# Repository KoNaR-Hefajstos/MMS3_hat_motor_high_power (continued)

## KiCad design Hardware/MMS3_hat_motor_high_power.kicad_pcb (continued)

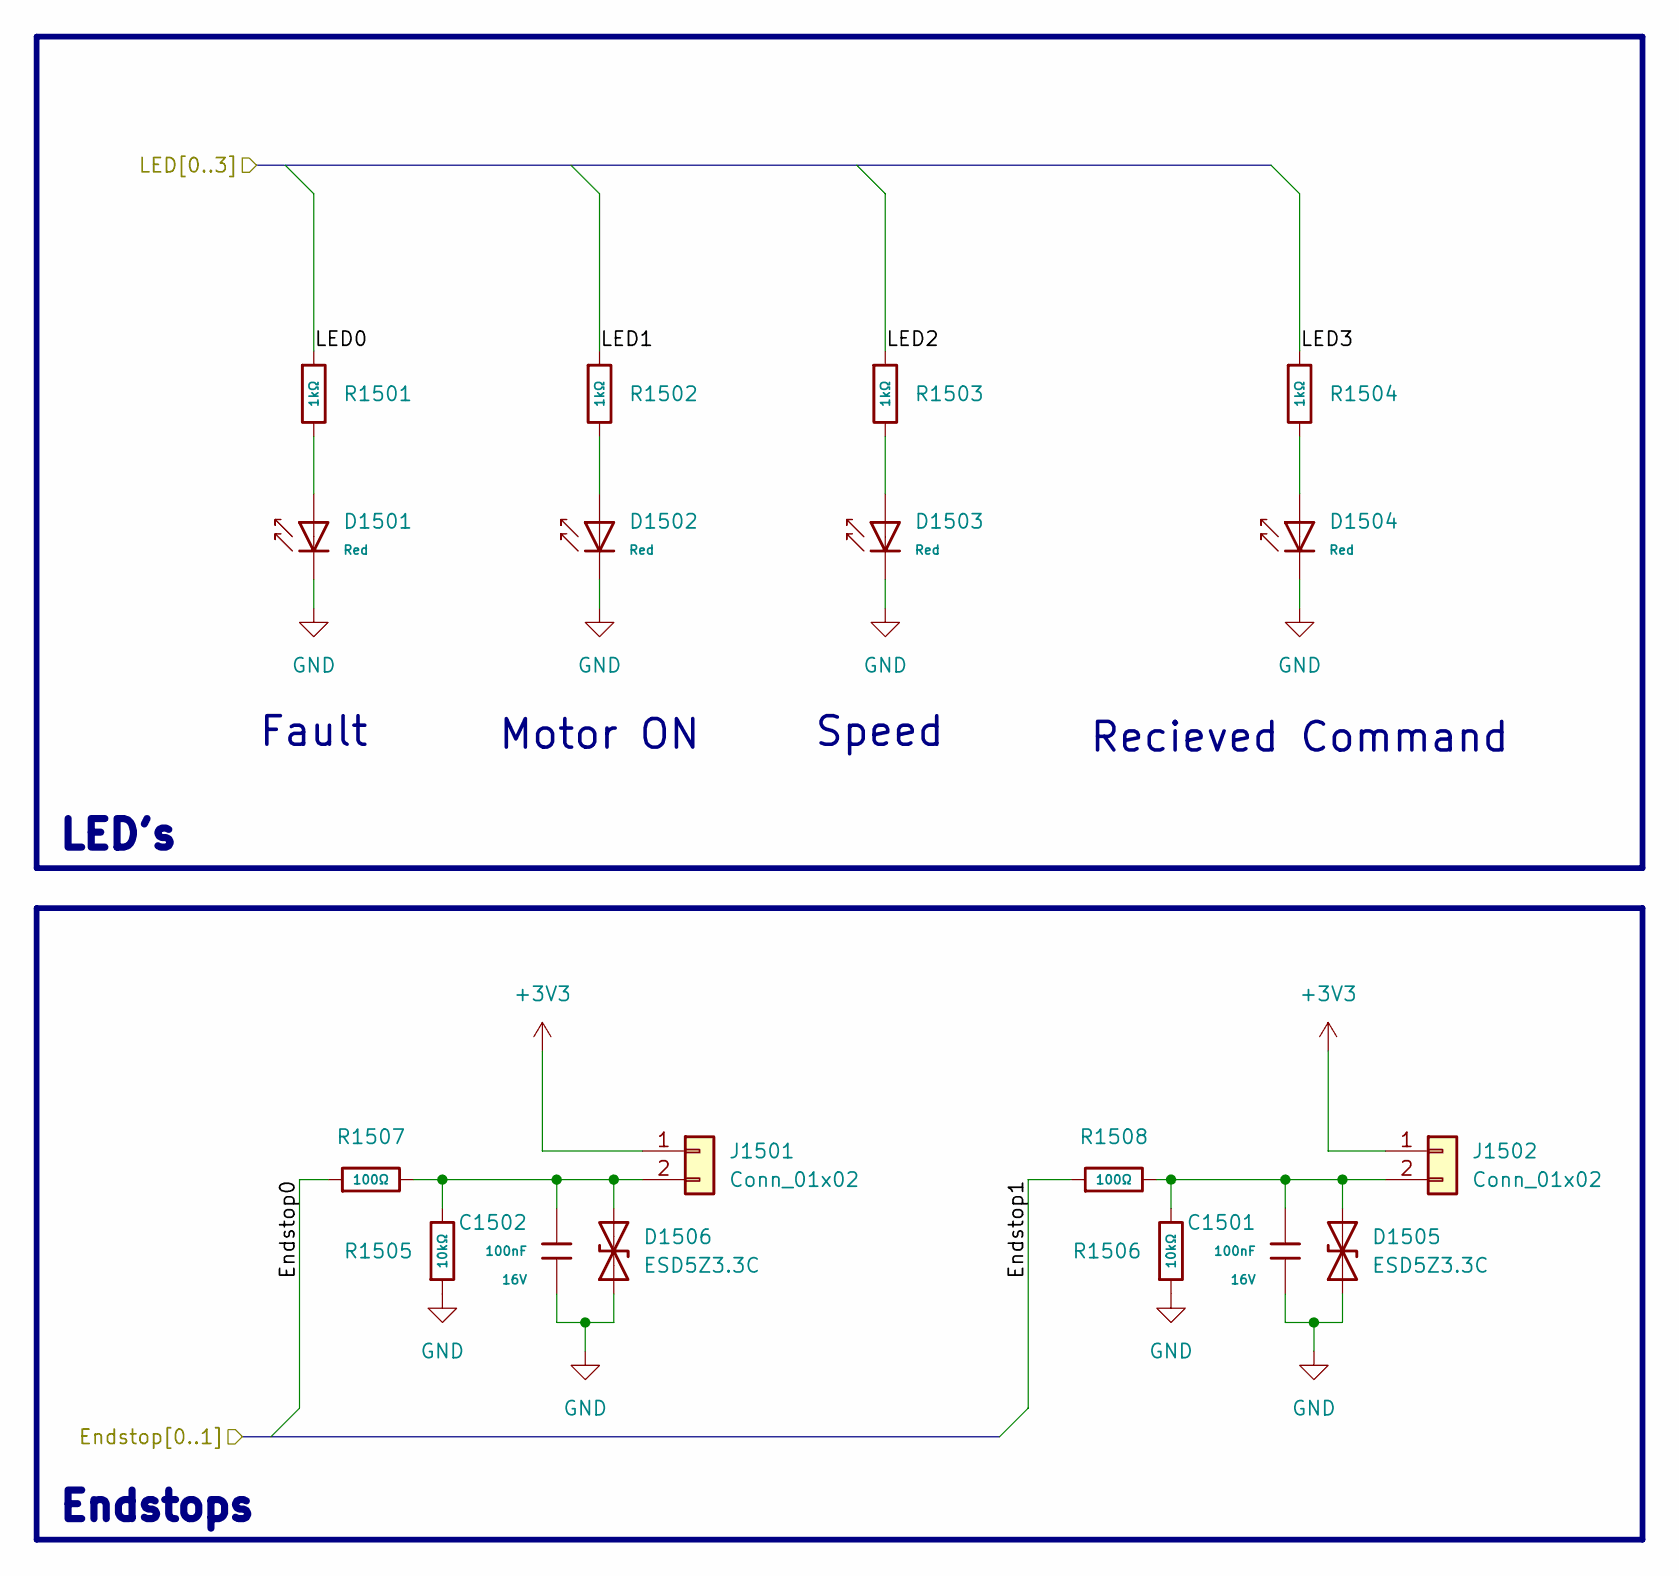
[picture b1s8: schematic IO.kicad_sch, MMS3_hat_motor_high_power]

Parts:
C1501, C1502: 100nF; C_0402; Voltage Rated 16V; Tolerance ±10%; Part CL05B104KO5NNNC; LCSC C1525
D1501, D1502, D1503, D1504: Red; D_0603; Part KT-0603R; LCSC C2286
D1505, D1506: ESD5Z3.3C; D_SOD-523; LCSC C502551
J1501, J1502: Conn_01x02; JST_XH_S2B-XH-A-1_1x02_P2.50mm_Horizontal
R1501, R1502, R1503, R1504: 1kΩ; R_0402; Overload Voltage (Max) 50V; Tolerance ±1%; Part 0402WGF1001TCE; LCSC C11702
R1505, R1506: 10kΩ; R_0402; Overload Voltage (Max) 50V; Tolerance ±1%; Part 0402WGF1002TCE; LCSC C25744
R1507, R1508: 100Ω; R_0402; Overload Voltage (Max) 50V; Tolerance ±1%; Part 0402WGF1000TCE; LCSC C25076

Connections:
+3V3: J1501.1, J1502.1; also elsewhere on the board
/User Area/CH32V305RBT6/GPIOB6: R1507.1; also elsewhere on the board
/User Area/CH32V305RBT6/GPIOB7: R1508.1; also elsewhere on the board
/User Area/CH32V305RBT6/GPIOB8: R1501.1; also elsewhere on the board
/User Area/CH32V305RBT6/GPIOB9: R1502.1; also elsewhere on the board
/User Area/CH32V305RBT6/GPIOB10: R1503.1; also elsewhere on the board
/User Area/CH32V305RBT6/GPIOB11: R1504.1; also elsewhere on the board
GND: C1501.2, C1502.2, D1501.1, D1502.1, D1503.1, D1504.1, D1505.1 (A1), D1506.1 (A1), R1505.1, R1506.1; also elsewhere on the board
unnamed: D1501.2, R1501.2
unnamed: D1502.2, R1502.2
unnamed: D1503.2, R1503.2
unnamed: D1504.2, R1504.2
unnamed: C1501.1, D1505.2 (A2), J1502.2, R1506.2, R1508.2
unnamed: C1502.1, D1506.2 (A2), J1501.2, R1505.2, R1507.2

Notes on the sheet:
LED's
Fault
Speed
Recieved Command
Motor ON
Endstops

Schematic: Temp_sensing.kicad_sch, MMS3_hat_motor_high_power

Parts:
R1401: 10kΩ; R_0402; Overload Voltage (Max) 50V; Tolerance ±1%; Part 0402WGF1002TCE; LCSC C25744
TH1401: NTC 10kΩ; R_0402; LCSC C77131

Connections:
+3V3: TH1401.1; also elsewhere on the board
/User Area/CH32V305RBT6/GPIOA3: R1401.1, TH1401.2; also elsewhere on the board
GND: R1401.2; also elsewhere on the board

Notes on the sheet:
BEHOLD! THE TEMPERATURE SENSING MACHINATIONS!

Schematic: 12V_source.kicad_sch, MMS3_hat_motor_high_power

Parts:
C1601: 33nF; C_0603; Voltage Rated 50V; Tolerance ±10%; Part CL10B333KB8NNNC; LCSC C21117
C1602: 33uF; CP_Radial_D10.0mm_P5.00mm; LCSC C56131621
C1603: 100uF; CP_Radial_D6.3mm_P2.50mm; LCSC C48935344
D1601: SS210; D_SMA; Forward Voltage (Vf@If) 850mV@2A; Reverse Voltage (Vr) 100V; Part SS210; LCSC C14996
L1601: SMDRI127-681MT; L_SXN_SMDRI127; MPN SMDRI127-681MT; LCSC Part C72434
R1601: 30kΩ; R_0603; Overload Voltage (Max) 75V; Tolerance ±1%; Part 0603WAF3002T5E; LCSC C22984
R1602: 3,48kΩ; R_0603; LCSC C2998120
U1602: XL7005A; SOIC-8-1EP_3.9x4.9mm_P1.27mm_EP2.41x3.3mm; MPN XL7005A; LCSC Part C50848

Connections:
+12V: C1601.1, C1603.1, L1601.2, R1601.1; also elsewhere on the board
/User Area/VIN: C1602.1, U1602.1 (VIN); also elsewhere on the board
GND: C1602.2, C1603.2, D1601.2, R1602.2, U1602.4 (EN), U1602.5 (GND), U1602.6 (GND), U1602.7 (GND), U1602.8 (GND), U1602.9; also elsewhere on the board
unnamed: C1601.2, R1601.2, R1602.1, U1602.3 (FB)
unnamed: D1601.1, L1601.1, U1602.2 (SW)

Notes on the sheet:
100% duty capable -> 12V = short

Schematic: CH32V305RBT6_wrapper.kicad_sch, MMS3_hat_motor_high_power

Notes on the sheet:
SPI/TIM for Encoder
CHECK IF TIM CHANNELS FOR MOTOR ARE GOOD (IF EACH ONE IS TIMxCHx + TIMxCHxN
ChainBus SPI
Mosfets & EN
USE TIM10 or SPI3
0-5 for BLDC 0-7 for Stepper
LEFT User usable GPIO
ADC's
LED's & Endstops
USE SPI1
MCU
USE TIM1 and TIM3

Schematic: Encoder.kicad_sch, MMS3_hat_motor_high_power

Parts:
D1301: 1SMA4729A; D_DO-214AC(SMA); Part 1SMA4729A; LCSC C19077475
D1302, D1303, D1304, D1305: ESD5Z3.3C; D_SOD-523; LCSC C502551
J1301: Conn_01x06; JST_XH_S6B-XH-A_1x06_P2.50mm_Horizontal
R1301, R1302, R1303, R1304: 100Ω; R_0402; Overload Voltage (Max) 50V; Tolerance ±1%; Part 0402WGF1000TCE; LCSC C25076

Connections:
+3V3: D1301.1, J1301.2; also elsewhere on the board
/User Area/CH32V305RBT6/GPIOA15: R1301.1; also elsewhere on the board
/User Area/CH32V305RBT6/GPIOB3: R1304.1; also elsewhere on the board
/User Area/CH32V305RBT6/GPIOB4: R1302.1; also elsewhere on the board
/User Area/CH32V305RBT6/GPIOB5: R1303.1; also elsewhere on the board
GND: D1301.2, D1302.1 (A1), D1303.1 (A1), D1304.1 (A1), D1305.1 (A1), J1301.1; also elsewhere on the board
unnamed: D1302.2 (A2), J1301.6, R1301.2
unnamed: D1303.2 (A2), J1301.5, R1302.2
unnamed: D1304.2 (A2), J1301.4, R1303.2
unnamed: D1305.2 (A2), J1301.3, R1304.2

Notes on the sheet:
Encoder Connector

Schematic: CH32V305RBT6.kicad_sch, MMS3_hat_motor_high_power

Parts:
C1101: 10uF; C_0603; Voltage Rated 10V; Tolerance ±10%; Part CL10A106KP8NNNC; LCSC C19702
C1102, C1109: 100nF; C_0402; Voltage Rated 50V; Tolerance ±10%; Part CL05B104KB54PNC; LCSC C307331
C1103, C1111: 22pF; C_0402; Voltage Rated 50V; Tolerance ±5%; Part 0402CG220J500NT; LCSC C1555
C1104, C1108: 12pF; C_0402; Voltage Rated 50V; Tolerance ±5%; Part 0402CG120J500NT; LCSC C1547
C1105, C1107, C1110, C1113, C1114: 100nF; C_0402; Voltage Rated 16V; Tolerance ±10%; Part CL05B104KO5NNNC; LCSC C1525
C1106, C1112: 10uF; C_0402; Voltage Rated 6.3V; Tolerance ±20%; Part CL05A106MQ5NUNC; LCSC C15525
D1101: Yellow; D_0603; Forward Voltage (VF) 1.6V~2.6V; Part NCD0603Y2; LCSC C89811
FB1101: FB_0603; Current Rating 200mA; Tolerance ±25%; Part GZ1608D601TF; LCSC C1002
J1101: WCH Link; PinSocket_2x05_P2.54mm_Vertical
R1101: 0Ω; R_0402; Overload Voltage (Max) 50V; Tolerance ±1%; Part 0402WGF0000TCE; LCSC C17168
R1102, R1103, R1104, R1106: 10kΩ; R_0402; Overload Voltage (Max) 50V; Tolerance ±1%; Part 0402WGF1002TCE; LCSC C25744
R1105: 10kΩ; R_0402; Overload Voltage (Max) 50V; Tolerance ±1%; Part 0402WGF1002TCE; LCSC C25744; not fitted
R1107: 1kΩ; R_0402; Overload Voltage (Max) 50V; Tolerance ±1%; Part 0402WGF1001TCE; LCSC C11702
S1101, S1102, S1103: Tactile Button, 160gf; SW_TS-1088-AR02016; Voltage Rating (Dc) 12V; Part TS-1088-AR02016; LCSC C720477
TP1101, TP1102: TestPoint; TestPoint_Pad_D1.0mm
U1101: CH32V305RBT6; C5187529_LQFP-64_L10_0-W10_0-P0_50-LS12_0-BL; LCSC C5187529
X1101: X322525MOB4SI; OSC-SMD_4P-L3.2-W2.5-BL; Frequency Tolerance ±10ppm; Part X322525MOB4SI; LCSC C9006
X1102: Q13FC1350000400; FC-135R_L3.2-W1.5; Frequency Tolerance ±20ppm; Part Q13FC13500004; LCSC C32346

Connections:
+3V3: C1101.1, C1102.1, C1105.1, C1106.1, C1107.1, C1110.1, FB1101.1, J1101.8, R1101.1, R1104.1, R1105.1, S1101.1 (A), S1102.1 (A), TP1101.1 (1_1), U1101.19 (VDD_4), U1101.32 (VIO_1), U1101.48 (VDD_2), U1101.64 (VIO_3); also elsewhere on the board
+5V: J1101.10; also elsewhere on the board
/User Area/ADC0: U1101.8 (PC0/ADC10); also elsewhere on the board
/User Area/ADC1: U1101.9 (PC1/ADC11); also elsewhere on the board
/User Area/ADC2: U1101.10 (PC2/ADC12); also elsewhere on the board
/User Area/ADC3: U1101.11 (PC3/ADC13); also elsewhere on the board
/User Area/ADC4: U1101.24 (PC4/ADC14); also elsewhere on the board
/User Area/ADC5: U1101.25 (PC5/ADC15); also elsewhere on the board
/User Area/ADC6: U1101.15 (PA1/ADC1); also elsewhere on the board
/User Area/ADC7: U1101.16 (PA2/ADC2); also elsewhere on the board
/User Area/CH32V305RBT6/CH32V305RBT6 minimal circuit/BOOT0: R1103.1, S1102.2 (B), U1101.60 (BOOT0)
/User Area/CH32V305RBT6/CH32V305RBT6 minimal circuit/NRST: C1114.1, J1101.9, R1104.2, S1103.1 (A), U1101.7 (NRST)
/User Area/CH32V305RBT6/CH32V305RBT6 minimal circuit/OSC32IN: C1104.1, U1101.3 (PC14/OSC32IN), X1102.1
/User Area/CH32V305RBT6/CH32V305RBT6 minimal circuit/OSC32OUT: C1108.1, U1101.4 (PC15/OSC32OUT), X1102.2
/User Area/CH32V305RBT6/CH32V305RBT6 minimal circuit/OSCIN: C1103.1, U1101.5 (OSC_IN/PD0), X1101.1 (OSC)
/User Area/CH32V305RBT6/CH32V305RBT6 minimal circuit/OSCOUT: C1111.1, U1101.6 (OSC_OUT/PD1), X1101.3 (OSC)
/User Area/CH32V305RBT6/CH32V305RBT6 minimal circuit/PB2/BOOT1: R1105.2, R1106.1, U1101.28 (PB2/BOOT1)
/User Area/CH32V305RBT6/CH32V305RBT6 minimal circuit/PC13/TAMPER-RTC: R1102.1, S1101.2 (B), U1101.2 (PC13/TAMPER-RTC)
/User Area/CH32V305RBT6/CH32V305RBT6 minimal circuit/PD2: R1107.1, U1101.54 (PD2)
/User Area/CH32V305RBT6/CH32V305RBT6 minimal circuit/SWCLK: J1101.2, U1101.49 (PA14/SWCLK)
/User Area/CH32V305RBT6/CH32V305RBT6 minimal circuit/SWDIO: J1101.4, U1101.46 (PA13/SWDIO)
/User Area/CH32V305RBT6/CH32V305RBT6 minimal circuit/UART4_RX: J1101.3, U1101.52 (PC11)
/User Area/CH32V305RBT6/CH32V305RBT6 minimal circuit/UART4_TX: J1101.1, U1101.51 (PC10)
/User Area/CH32V305RBT6/CH32V305RBT6 minimal circuit/VDDA: C1109.1, C1112.1, FB1101.2, TP1102.1 (1_1), U1101.13 (VDDA)
/User Area/CH32V305RBT6/GPIOA0: U1101.14 (PA0/WKUP/ADC0); also elsewhere on the board
/User Area/CH32V305RBT6/GPIOA3: U1101.17 (PA3/ADC3); also elsewhere on the board
/User Area/CH32V305RBT6/GPIOA11: U1101.44 (PA11/USB1DM)
/User Area/CH32V305RBT6/GPIOA12: U1101.45 (PA12/USB1DP)
/User Area/CH32V305RBT6/GPIOA15: U1101.50 (PA15); also elsewhere on the board
/User Area/CH32V305RBT6/GPIOB3: U1101.55 (PB3); also elsewhere on the board
/User Area/CH32V305RBT6/GPIOB4: U1101.56 (PB4); also elsewhere on the board
/User Area/CH32V305RBT6/GPIOB5: U1101.57 (PB5); also elsewhere on the board
/User Area/CH32V305RBT6/GPIOB6: U1101.58 (PB6/USB2DM); also elsewhere on the board
/User Area/CH32V305RBT6/GPIOB7: U1101.59 (PB7/USB2DP); also elsewhere on the board
/User Area/CH32V305RBT6/GPIOB8: U1101.61 (PB8); also elsewhere on the board
/User Area/CH32V305RBT6/GPIOB9: U1101.62 (PB9); also elsewhere on the board
/User Area/CH32V305RBT6/GPIOB10: U1101.29 (PB10); also elsewhere on the board
/User Area/CH32V305RBT6/GPIOB11: U1101.30 (PB11); also elsewhere on the board
/User Area/CH32V305RBT6/GPIOB12: U1101.33 (PB12); also elsewhere on the board
/User Area/CH32V305RBT6/GPIOC6: U1101.37 (PC6)
/User Area/CH32V305RBT6/GPIOC7: U1101.38 (PC7)
/User Area/CH32V305RBT6/GPIOC8: U1101.39 (PC8)
/User Area/CH32V305RBT6/GPIOC9: U1101.40 (PC9)
/User Area/CH32V305RBT6/GPIOC12: U1101.53 (PC12)
/User Area/Chainbus.CS: U1101.20 (PA4/ADC4/DAC0); also elsewhere on the board
/User Area/Chainbus.MISO: U1101.22 (PA6/ADC6); also elsewhere on the board
/User Area/Chainbus.MOSI: U1101.23 (PA7/ADC7); also elsewhere on the board
/User Area/Chainbus.SCK: U1101.21 (PA5/ADC5/DAC1); also elsewhere on the board
/User Area/Mosfet0: U1101.41 (PA8); also elsewhere on the board
/User Area/Mosfet1: U1101.34 (PB13); also elsewhere on the board
/User Area/Mosfet2: U1101.42 (PA9); also elsewhere on the board
/User Area/Mosfet3: U1101.35 (PB14); also elsewhere on the board
/User Area/Mosfet4: U1101.43 (PA10); also elsewhere on the board
/User Area/Mosfet5: U1101.36 (PB15); also elsewhere on the board
/User Area/Mosfet6: U1101.26 (PB0/ADC8); also elsewhere on the board
/User Area/Mosfet7: U1101.27 (PB1/ADC9); also elsewhere on the board
GND: C1101.2, C1102.2, C1103.2, C1104.2, C1105.2, C1106.2, C1107.2, C1108.2, C1109.2, C1110.2, C1111.2, C1112.2, C1113.2, C1114.2, D1101.1, J1101.6, R1102.2, R1103.2, R1106.2, S1103.2 (B), U1101.12 (VSSA), U1101.18 (VSS_4), U1101.31 (VSS_1), U1101.47 (VSS_2), U1101.63 (VSS_3), X1101.2 (GND), X1101.4 (GND); also elsewhere on the board
unnamed: D1101.2, R1107.2
unnamed: C1113.1, R1101.2, U1101.1 (VBAT)

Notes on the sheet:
NRST
User usable GPIO
VDDA
TDO TDI
Crystals
User IO
Boot pins
Decoupling caps
Programming & debugging
WCH Link-E: RX - pin 1 TX - pin 3

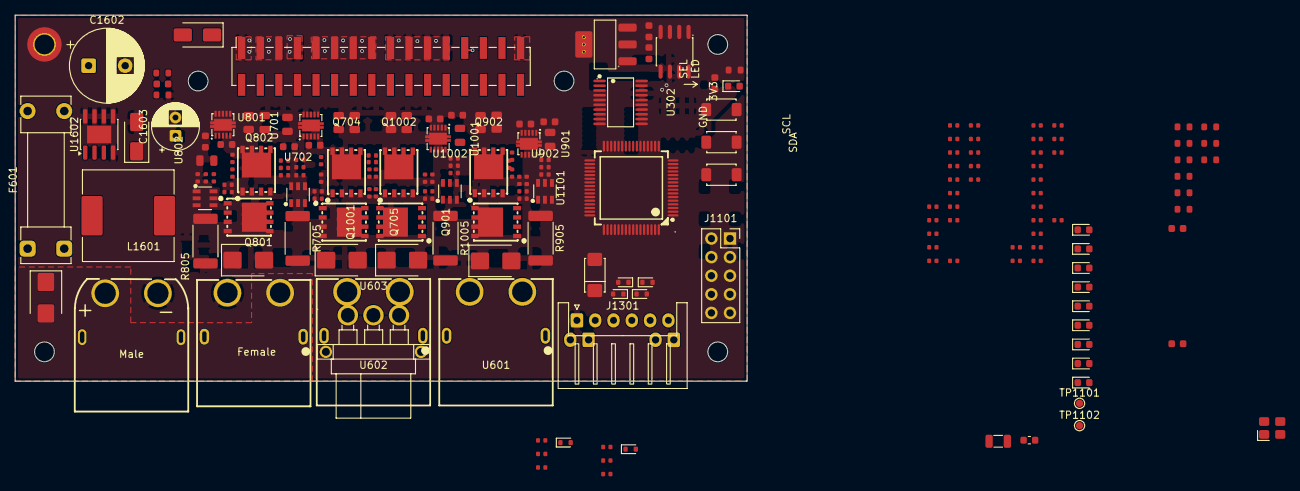
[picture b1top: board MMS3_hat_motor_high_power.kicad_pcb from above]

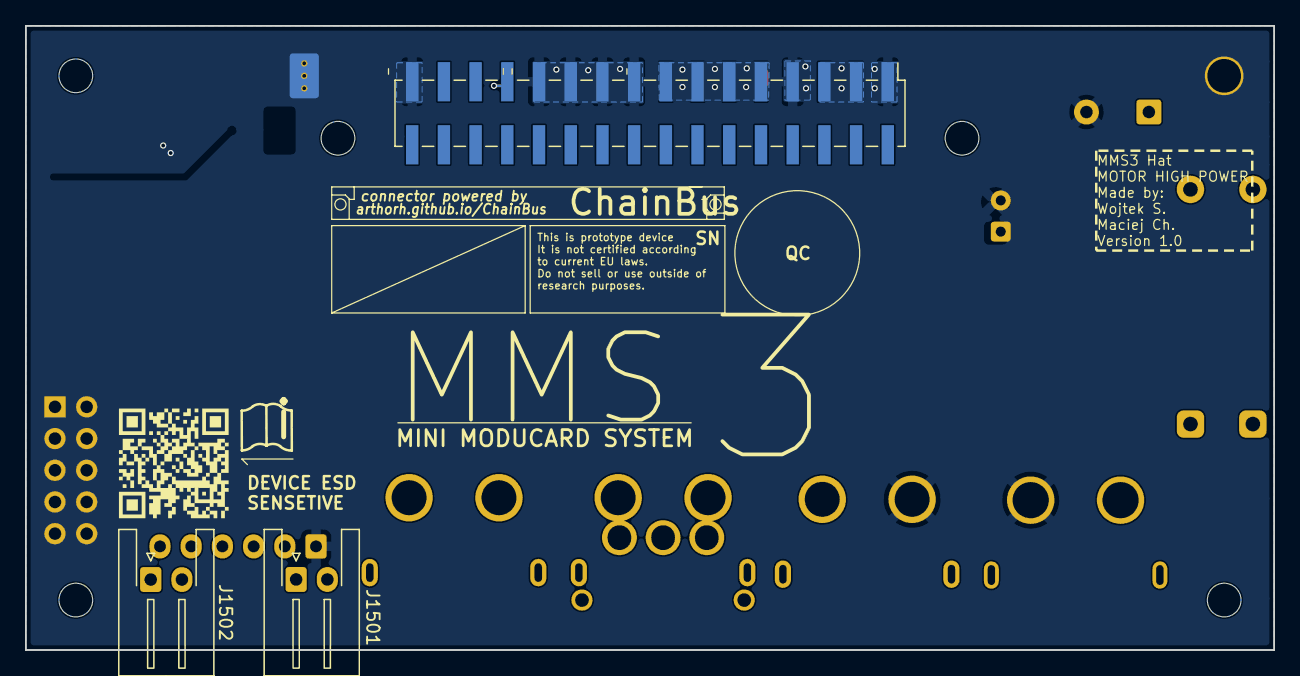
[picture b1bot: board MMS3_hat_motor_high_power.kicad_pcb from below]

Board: 2 copper layers, 100.0 x 50.0 mm, 198 parts (3 on the bottom side), 126 nets.
